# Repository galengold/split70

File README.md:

# split70

QMK firmware, CAD files, and PCB for the Split70 keyboard

For more information, see my [build log](http://galengold.me/split70/)

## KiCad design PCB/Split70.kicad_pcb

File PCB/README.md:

# PCB

Developed with [KiCAD](http://kicad.org).

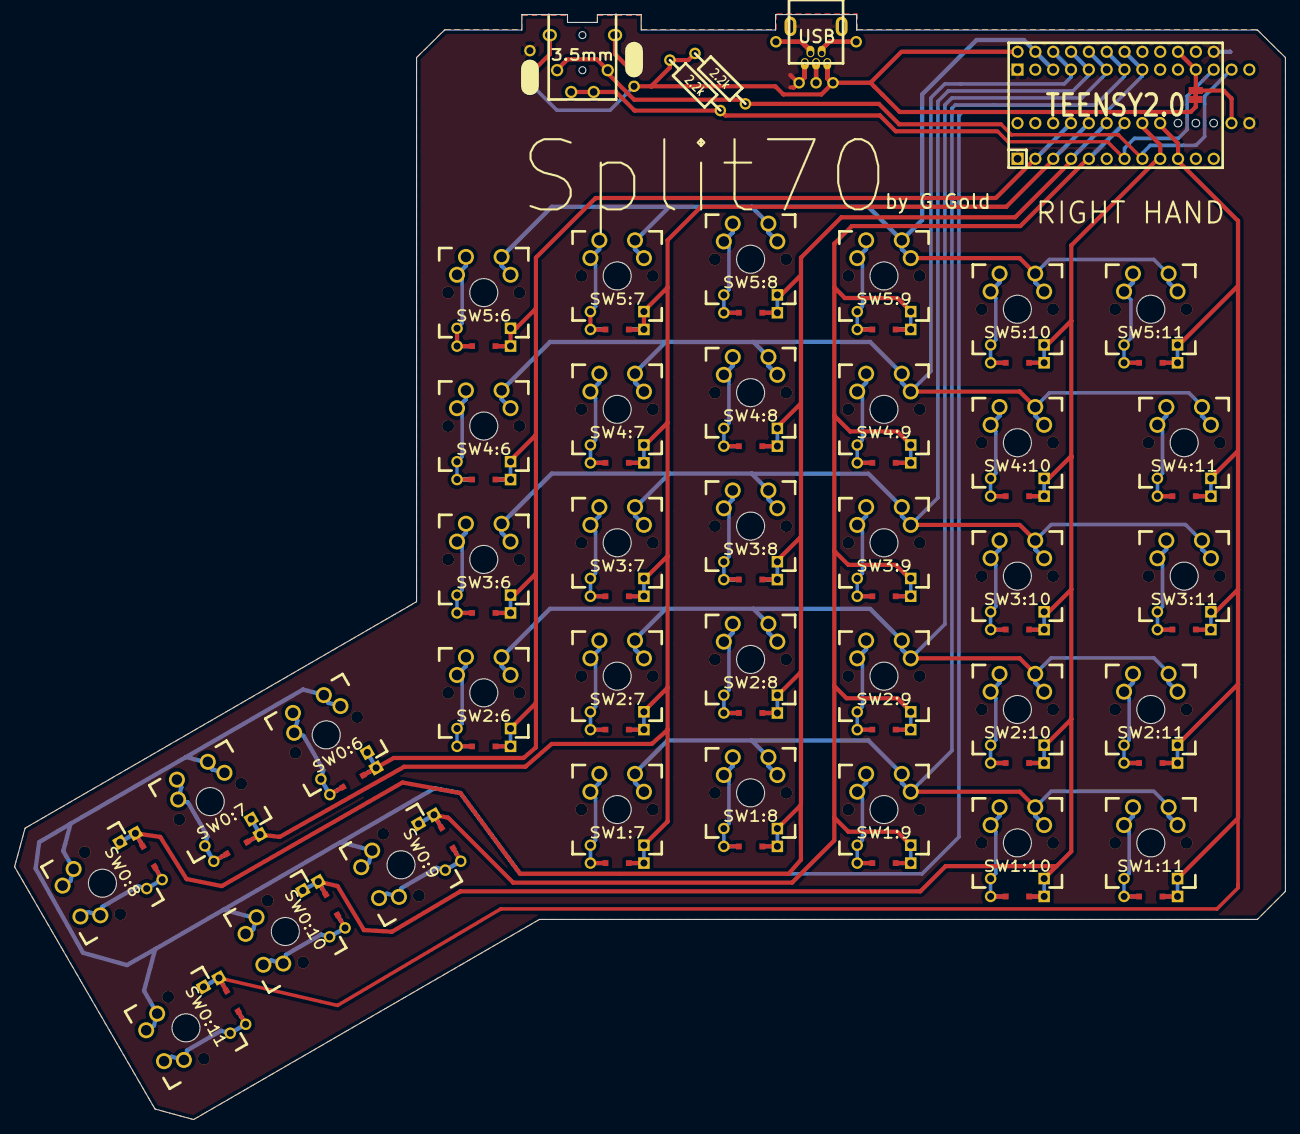
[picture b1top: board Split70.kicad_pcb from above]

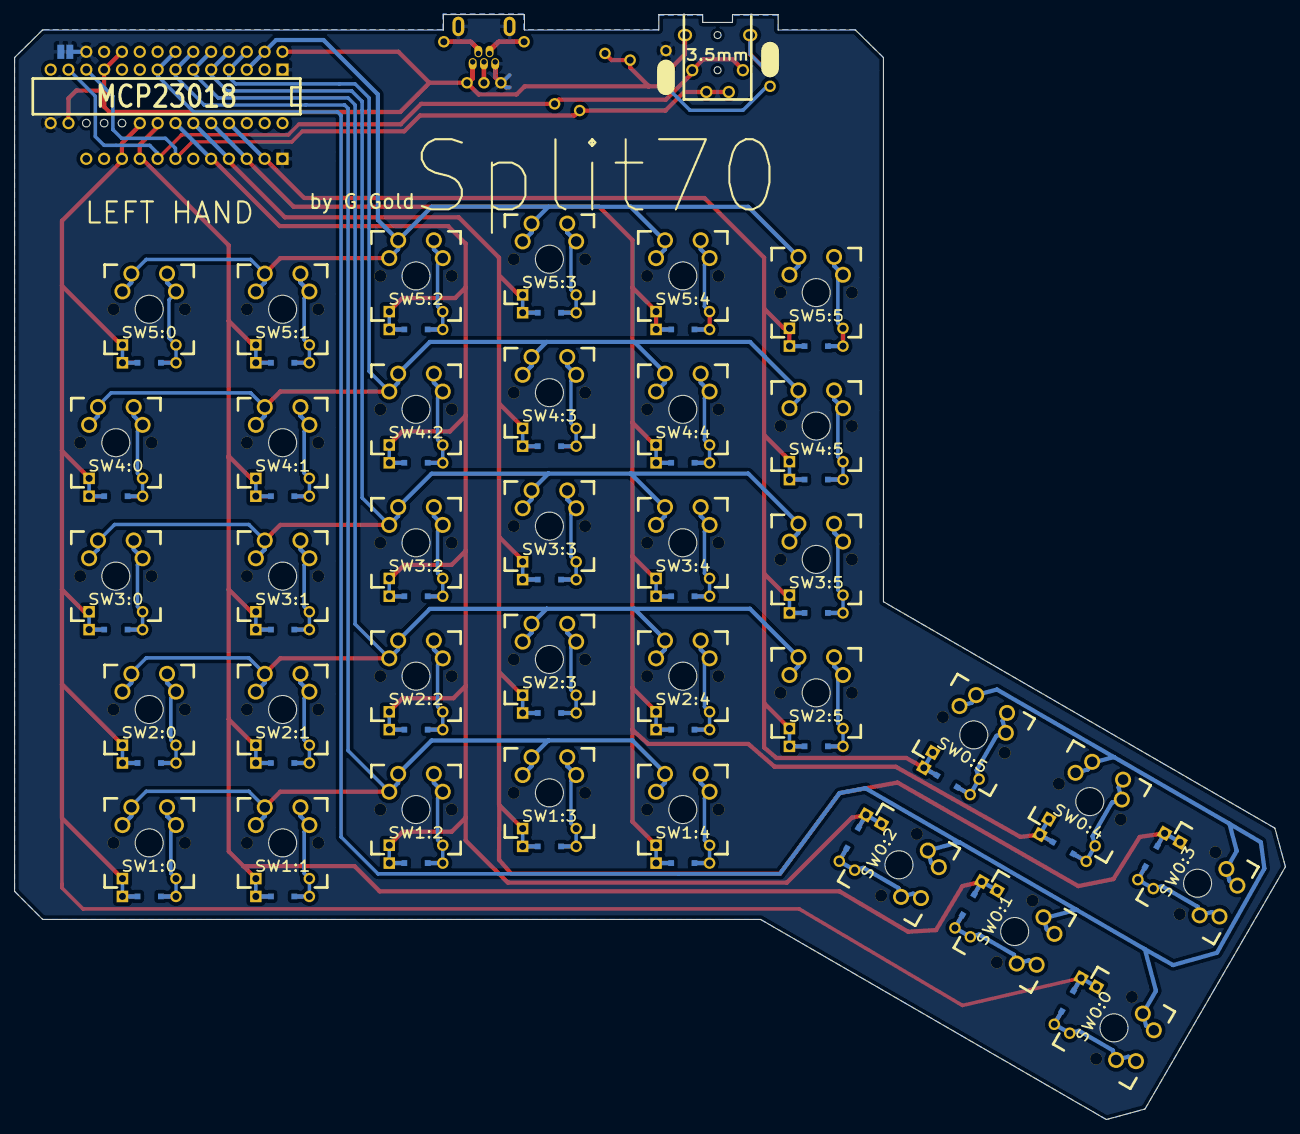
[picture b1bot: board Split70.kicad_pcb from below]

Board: 2 copper layers, 181.0 x 157.4 mm, 45 parts (3 on the bottom side), 53 nets.

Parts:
J1: USB; USBMINImod
J2: 3.5mm; 4pin35mmAudio
J3, J4: JMP; 100PITCH1X3
JP1, JP2: JUMPER; GAP
R1, R2: 2.2k; RESISTOR
SW0:6: SW0:5; MX_FLIP_DIODE
SW0:7: SW0:4; MX_FLIP_DIODE
SW0:8: SW0:3; MX_FLIP_DIODE
SW0:9: SW0:2; MX_FLIP_DIODE
SW0:10: SW0:1; MX_FLIP_DIODE
SW0:11: SW0:0; MX_FLIP_DIODE
SW1:7: SW1:4; MX_FLIP_DIODE
SW1:8: SW1:3; MX_FLIP_DIODE
SW1:9: SW1:2; MX_FLIP_DIODE
SW1:10: SW1:1; MX_FLIP_DIODE
SW1:11: SW1:0; MX_FLIP_DIODE
SW2:6: SW2:5; MX_FLIP_DIODE
SW2:7: SW2:4; MX_FLIP_DIODE
SW2:8: SW2:3; MX_FLIP_DIODE
SW2:9: SW2:2; MX_FLIP_DIODE
SW2:10: SW2:1; MX_FLIP_DIODE
SW2:11: SW2:0; MX_FLIP_DIODE
SW3:6: SW3:5; MX_FLIP_DIODE
SW3:7: SW3:4; MX_FLIP_DIODE
SW3:8: SW3:3; MX_FLIP_DIODE
SW3:9: SW3:2; MX_FLIP_DIODE
SW3:10: SW3:1; MX_FLIP_DIODE
SW3:11: SW3:0; MX_FLIP_DIODE
SW4:6: SW4:5; MX_FLIP_DIODE
SW4:7: SW4:4; MX_FLIP_DIODE
SW4:8: SW4:3; MX_FLIP_DIODE
SW4:9: SW4:2; MX_FLIP_DIODE
SW4:10: SW4:1; MX_FLIP_DIODE
SW4:11: SW4:0; MX_FLIP_DIODE
SW5:6: SW5:5; MX_FLIP_DIODE
SW5:7: SW5:4; MX_FLIP_DIODE
SW5:8: SW5:3; MX_FLIP_DIODE
SW5:9: SW5:2; MX_FLIP_DIODE
SW5:10: SW5:1; MX_FLIP_DIODE
SW5:11: SW5:0; MX_FLIP_DIODE
U1: TEENSY2.0; TEENSY_2.0
U2: MCP23018; DIP28_300

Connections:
/COL0: SW0:11.4, SW1:11.4, SW2:11.4, SW3:11.4, SW4:11.4, SW5:11.4, U1.10, U2.20
/COL1: SW0:10.4, SW1:10.4, SW2:10.4, SW3:10.4, SW4:10.4, SW5:10.4, U1.9, U2.21
/COL2: SW0:9.4, SW1:9.4, SW2:9.4, SW3:9.4, SW4:9.4, SW5:9.4, U1.5, U2.22
/COL3: SW0:8.4, SW1:8.4, SW2:8.4, SW3:8.4, SW4:8.4, SW5:8.4, U1.4, U2.23
/COL4: SW0:7.4, SW1:7.4, SW2:7.4, SW3:7.4, SW4:7.4, SW5:7.4, U1.3, U2.24
/COL5: SW0:6.4, SW2:6.4, SW3:6.4, SW4:6.4, SW5:6.4, U1.2, U2.25
/ROW0: SW0:6.1, SW0:7.1, SW0:8.1, SW0:9.1, SW0:10.1, SW0:11.1, U1.23, U2.8
/ROW1: SW1:7.1, SW1:8.1, SW1:9.1, SW1:10.1, SW1:11.1, U1.24, U2.7
/ROW2: SW2:6.1, SW2:7.1, SW2:8.1, SW2:9.1, SW2:10.1, SW2:11.1, U1.25, U2.6
/ROW3: SW3:6.1, SW3:7.1, SW3:8.1, SW3:9.1, SW3:10.1, SW3:11.1, U1.26, U2.5
/ROW4: SW4:6.1, SW4:7.1, SW4:8.1, SW4:9.1, SW4:10.1, SW4:11.1, U1.27, U2.4
/ROW5: SW5:6.1, SW5:7.1, SW5:8.1, SW5:9.1, SW5:10.1, SW5:11.1, U1.28, U2.3
/SCLM: J2.3, J2.5, R2.2, U1.7, U2.12
/SDAM: J2.2, J2.6, R1.2, U1.8, U2.13
GND: J1.5, J1.6, J3.3, J4.3, JP2.1, SW0:6.0, SW0:7.0, SW0:8.0, SW0:9.0, SW0:10.0, SW0:11.0, SW1:7.0, SW1:8.0, SW1:9.0, SW1:10.0, SW1:11.0, SW2:6.0, SW2:7.0, SW2:8.0, SW2:9.0, SW2:10.0, SW2:11.0, SW3:6.0, SW3:7.0, SW3:8.0, SW3:9.0, SW3:10.0, SW3:11.0, SW4:6.0, SW4:7.0, SW4:8.0, SW4:9.0, SW4:10.0, SW4:11.0, SW5:6.0, SW5:7.0, SW5:8.0, SW5:9.0, SW5:10.0, SW5:11.0, U1.1, U1.18, U2.1, U2.15
unnamed: J2.1, J3.2
unnamed: J2.4, J4.2
unnamed: SW0:6.2, SW0:6.3
unnamed: SW0:7.2, SW0:7.3
unnamed: SW0:8.2, SW0:8.3
unnamed: SW0:9.2, SW0:9.3
unnamed: SW0:10.2, SW0:10.3
unnamed: SW0:11.2, SW0:11.3
unnamed: SW1:7.2, SW1:7.3
unnamed: SW1:8.2, SW1:8.3
unnamed: SW1:9.2, SW1:9.3
unnamed: SW1:10.2, SW1:10.3
unnamed: SW1:11.2, SW1:11.3
unnamed: SW2:6.2, SW2:6.3
unnamed: SW2:7.2, SW2:7.3
unnamed: SW2:8.2, SW2:8.3
unnamed: SW2:9.2, SW2:9.3
unnamed: SW2:10.2, SW2:10.3
unnamed: SW2:11.2, SW2:11.3
unnamed: SW3:6.2, SW3:6.3
unnamed: SW3:7.2, SW3:7.3
unnamed: SW3:8.2, SW3:8.3
unnamed: SW3:9.2, SW3:9.3
unnamed: SW3:10.2, SW3:10.3
unnamed: SW3:11.2, SW3:11.3
unnamed: SW4:6.2, SW4:6.3
unnamed: SW4:7.2, SW4:7.3
unnamed: SW4:8.2, SW4:8.3
unnamed: SW4:9.2, SW4:9.3
unnamed: SW4:10.2, SW4:10.3
unnamed: SW4:11.2, SW4:11.3
unnamed: SW5:6.2, SW5:6.3
unnamed: SW5:7.2, SW5:7.3
unnamed: SW5:8.2, SW5:8.3
unnamed: SW5:9.2, SW5:9.3
unnamed: SW5:10.2, SW5:10.3
unnamed: SW5:11.2, SW5:11.3
VCC: J1.1, J3.1, J4.1, JP1.1, R1.1, R2.1, U1.20, U1.29, U2.11, U2.16

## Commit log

2017-03-23 create site dir
2017-03-23 Set theme jekyll-theme-minimal
2017-03-24 added firmware, init PCB and case directories
2017-03-27 changed layout
2017-05-29 added split70
2017-06-05 updated stuff
2017-06-05 removed vim files and .build/
2017-06-05 I am an idiot
2017-06-05 changed map
2017-06-06 changed keymap
2017-06-12 removed GH site. will move to blog.
2017-06-12 added KLE files
2017-08-11 Added PCB files
2017-08-19 added case dxf files
2017-08-19 updated readmes
2017-08-20 added mousekeys on function layer
2017-09-02 added macros for Rocket League
2017-10-23 removed macros and capslock
2017-11-24 update keymap
